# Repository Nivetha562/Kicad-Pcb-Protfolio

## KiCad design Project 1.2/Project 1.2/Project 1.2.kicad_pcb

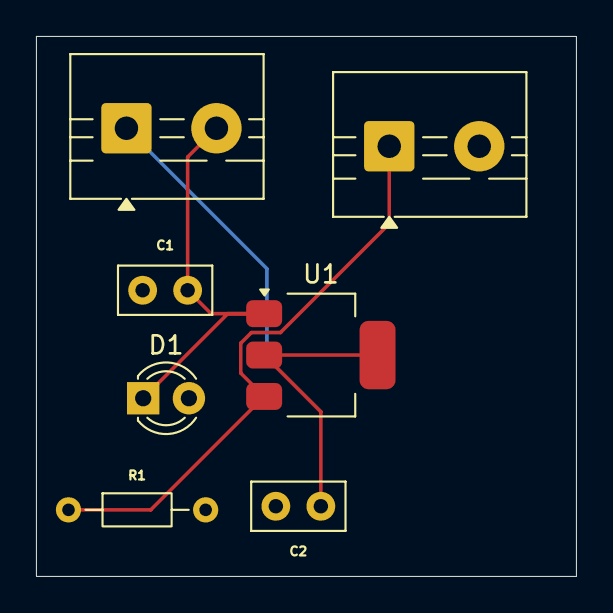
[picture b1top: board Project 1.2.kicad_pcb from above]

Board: 2 copper layers, 30.0 x 30.0 mm, 7 parts (0 on the bottom side), 4 nets.

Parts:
C1, C2: 10; C_Disc_D5.0mm_W2.5mm_P2.50mm
D1: LED; LED_D3.0mm_IRBlack
J1: 5v input; TerminalBlock_MaiXu_MX126-5.0-02P_1x02_P5.00mm
J2: 3.3 v output; TerminalBlock_MaiXu_MX126-5.0-02P_1x02_P5.00mm
R1: R_US; R_Axial_DIN0204_L3.6mm_D1.6mm_P7.62mm_Horizontal
U1: AMS1117-3.3; SOT-223-3_TabPin2

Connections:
/a: C1.1, J2.1, R1.1, U1.3 (VI)
/b: C2.1, J1.1, U1.2 (VO)
GND1: C1.2, C2.2, D1.1 (K), J1.2, J2.2, U1.1 (GND)
unnamed: D1.2 (A), R1.2
